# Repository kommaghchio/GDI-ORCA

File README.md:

A flight controller for a drone, with support for 2 servo motors, based on the Hack Club blueprint guide found here:
https://blueprint.hackclub.com/starter-projects/flightcontroller

I used KiCad, from which I used easyeda2kicad in order to get the footprints and schematic symbols, credited here:

https://github.com/uPesy/easyeda2kicad.py

It uses the STM32F722RET6 as the main brains.

Schematics:

PCB:

3D Board render:

BOM:
|Item                    |Qty|Supplier|Cost/item|Total Cost|link                                                                              |
|------------------------|---|--------|---------|----------|----------------------------------------------------------------------------------|
|USB-C 16 pin            |1  |LCSC    |$1.44    |$1.44     |https://www.lcsc.com/product-detail/C2765186.html?s_z=n_q_C2765186%2520USB-C      |
|C49441431 MicroSD       |1  |LCSC    |$0.44    |$0.44     |https://www.lcsc.com/product-detail/C49441431.html?s_z=n_q_C49441431%2520MicroSD  |
|C109322 TPS63070        |1  |LCSC    |$1.24    |$1.24     |https://www.lcsc.com/product-detail/C109322.html?s_z=n_q_C109322%2520TPS63070     |
|C5185863 LMR51430       |1  |LCSC    |$0.79    |$0.79     |https://www.lcsc.com/product-detail/C5185863.html?s_z=n_q_C5185863%2520LMR51430   |
|C544362 BQ25883         |1  |LCSC    |$4.26    |$4.26     |https://www.lcsc.com/product-detail/C544362.html?s_z=n_q_C544362%2520BQ25883      |
|C118207 STM32F722RET6   |1  |LCSC    |$11.29   |$11.29    |https://www.lcsc.com/product-detail/C118207.html?s_z=n_q_C118207%2520STM32F722RET6|
|C22459454 ICM-45686     |1  |LCSC    |$10.31   |$10.31    |https://www.lcsc.com/product-detail/C22459454.html?s_z=n_q_C22459454%2520ICM-45686|
|C22391138 BMP580        |1  |LCSC    |$1.21    |$1.21     |https://www.lcsc.com/product-detail/C22391138.html?s_z=n_q_C22391138%2520BMP580   |
|C2681587 5.8-ZSGT       |2  |LCSC    |$0.48    |$0.96     |https://www.lcsc.com/product-detail/C2681587.html?s_z=n_q_p_C2681587%25205.8-ZSGT |
|C7417180 1.5uH          |1  |LCSC    |$5.50    |$5.50     |https://www.lcsc.com/product-detail/C7417180.html?s_z=n_q_C7417180%25201.5uH      |
|C380178 5.6uH           |1  |LCSC    |$0.57    |$0.57     |https://www.lcsc.com/product-detail/C380178.html?s_z=n_q_C380178%25205.6uH        |
|C1857257 KC2520Z        |1  |LCSC    |$3.00    |$3.00     |https://www.lcsc.com/product-detail/C1857257.html?s_z=n_q_p_C1857257%2520KC2520Z  |
|PCB                     |1  |JLCPCB  |$9.20    |$9.20     |https://jlcpcb.com/                                                               |
|Estimated total shipping|1  |        |         |$9.45     |                                                                                  |

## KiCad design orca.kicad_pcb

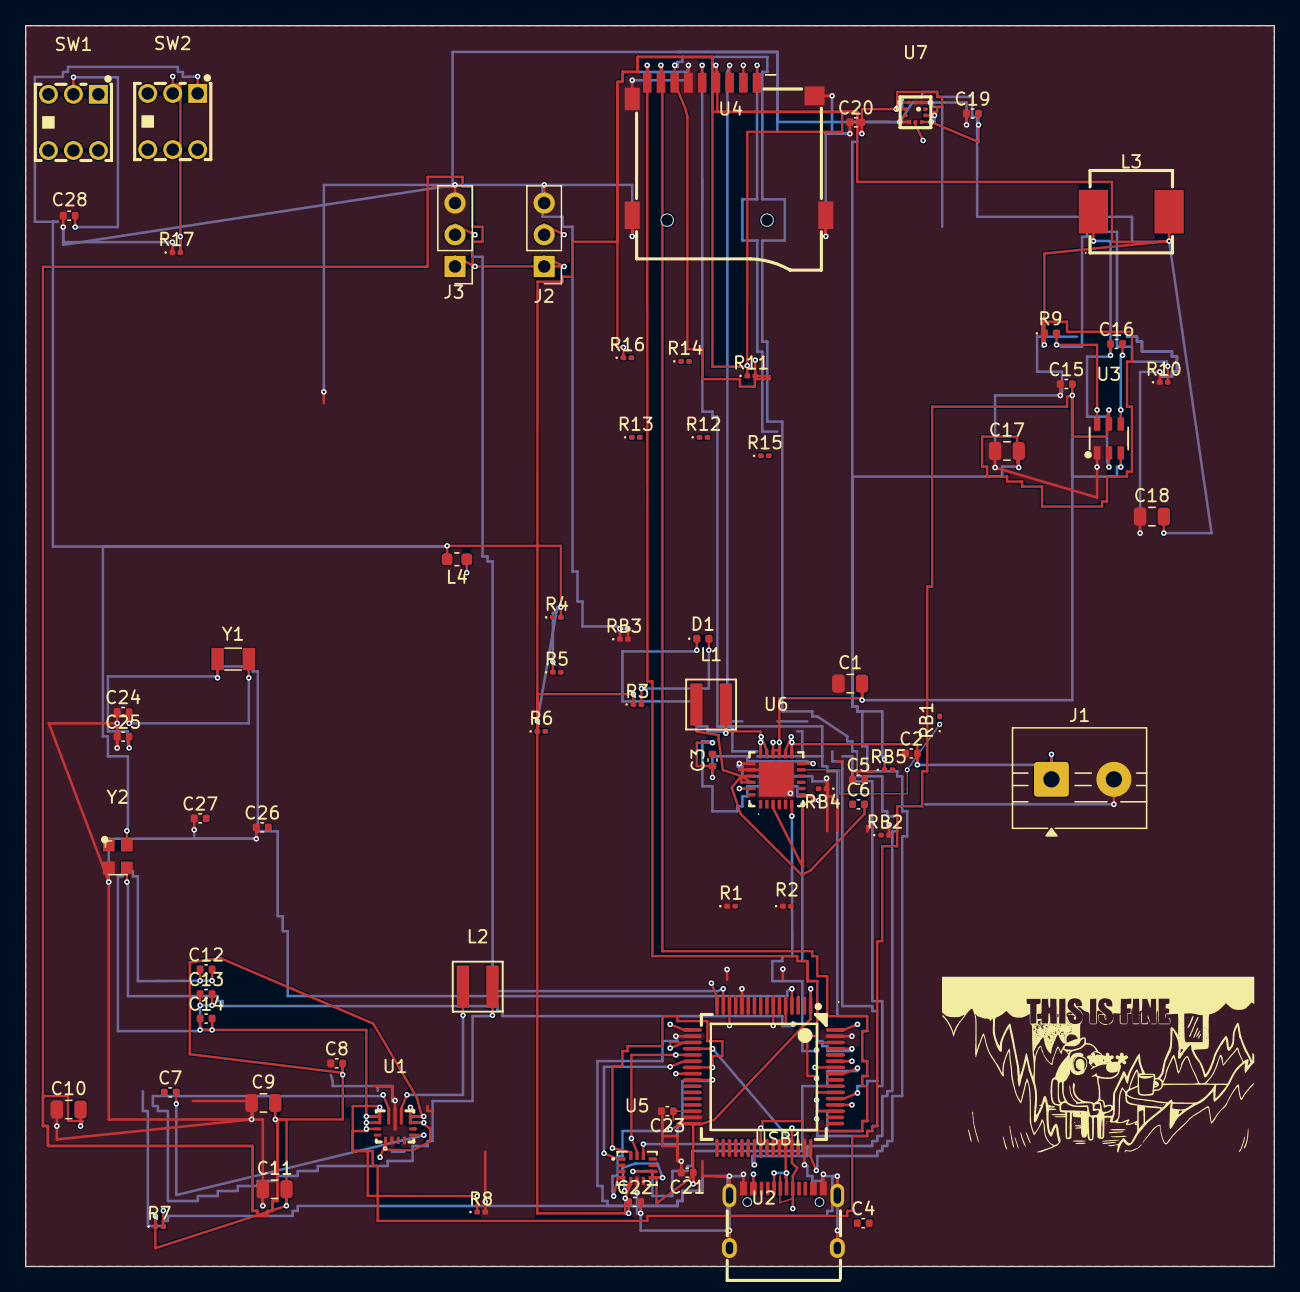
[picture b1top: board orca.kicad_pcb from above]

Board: 2 copper layers, 100.0 x 99.4 mm, 70 parts (0 on the bottom side), 51 nets.

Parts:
C1: 44uF; C_0805_2012Metric
C2, C6, C8, C12, C13, C14: 10uF; C_0402_1005Metric
C3: 47nF; C_0402_1005Metric
C4: 1nF; C_0402_1005Metric
C5: 10nF; C_0402_1005Metric
C7, C16, C19, C20, C21, C22, C28: 100nF; C_0402_1005Metric
C9, C10, C11, C17, C18: 22uF; C_0805_2012Metric
C15, C23: 2.2uF; C_0402_1005Metric
C24, C25: 6.8pF; C_0402_1005Metric
C26, C27: 20pF; C_0402_1005Metric
D1: LED; D_0402_1005Metric
J1: Screw_Terminal_01x02; TerminalBlock_MaiXu_MX126-5.0-02P_1x02_P5.00mm
J2, J3: Conn_01x03; PinHeader_1x03_P2.54mm_Vertical
L1, L2: 1.5 uH; 1.5uH
L3: 5.6uH
L4: FCM1608KF-601T03; L_0603_1608Metric
R1: 5.1K; D_0201_0603Metric
R2: 5.1k; D_0201_0603Metric
R3, R4, R5, R6, R7, R8, R11, R12, R13, R14, R15, R16, R17: 10K; D_0201_0603Metric
R9: 100K; D_0402_1005Metric
R10: 22.1K; D_0201_0603Metric
RB1: 5.23K; D_0201_0603Metric
RB2: 30.1K; D_0201_0603Metric
RB3, RB5: 10K; D_0201_0603Metric
RB4: 3B3; D_0201_0603Metric
SW1, SW2: SW_SPST; 5.8-ZSGT
U1: TPS63070RNMR; TPS63070
U2: STM32F722RET6
U3: LMR51430XDDCR; LMR51430
U4: JBL-102010052; MicroSD
U5: ICM-45686
U6: BQ25883RGER; BQ25883
U7: BMP580
USB1: TYPE-C 16PIN 2MD; USB-C
Y1: Q13FC1350000400; Crystal_SMD_3215-2Pin_3.2x1.5mm
Y2: KC2520Z

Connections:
+3.3V: C17.2, C18.2, C19.2, C20.2, C21.1, C22.1, L3.2, L4.2, R3.1, R4.2, R5.1, R6.1, R9.1, R11.1, R16.1, RB5.1, SW2.1 (A), U2.1 (VBAT), U2.19 (VDD), U2.32 (VDD), U2.48 (VDD), U2.64 (VDD), U4.4 (VDD), U5.5 (VDDIO), U5.8 (VDD), U7.1 (VDDIO), U7.5 (SDO), U7.6 (CSB), U7.10 (VDD), Y2.4 (VCC)
+5V: C8.2, C9.2, C10.2, C11.2, J2.1, J3.1, R7.1, U1.1 (PS/SYNC), U1.7 (Vout)
+BATT: C2.2, J1.1, U6.13 (BAT), U6.14 (BAT)
/BMP_INT: U2.24 (PC4), U7.7 (INT)
/BOOT: R17.2, SW2.2 (B), U2.60 (BOOT0)
/BQ_CE: U2.61 (PB8), U6.3 (~CE)
/BQ_INT: U2.62 (PB9), U6.6 (~INT)
/BTST: C3.2, U6.12 (BTST)
/HSE_IN: U2.5 (PH0-OSC_IN), Y2.3 (CLK)
/I2C_SCL: U2.58 (PB6), U6.5 (SCL), U7.2 (SCK)
/I2C_SDA: U2.59 (PB7), U6.4 (SDA), U7.4 (SDI)
/ICM_CS: U2.20 (PA4), U5.12 (AP_CS)
/ICM_INT1: U2.25 (PB0), U5.4 (INT1/INT)
/ICM_INT2: U2.57 (PB5), U5.9 (INT2/FSYNC/CLKIN)
/ICM_SCK: U2.21 (PA5), U5.13 (AP_SCL/AP_SCLK)
/ICM_SDI: U2.23 (PA7), U5.14 (AP_SDA/AP_SDIO/AP_SDI)
/ICM_SDO: U2.22 (PA6), U5.1 (AP_SDO/AP_AD0)
/LSE_IN: C24.2, U2.3 (PC14-OSC32_IN), Y1.1
/LSE_OUT: C25.2, U2.4 (PC15-OSC32_OUT), Y1.2
/RESET: C28.2, SW1.2 (B), U2.7 (NRST)
/SD_CD: U2.55 (PB3), U4.CD
/SD_CLK: U2.53 (PC12), U4.5 (CLK)
/SD_CMD: U2.54 (PD2), U4.3 (CMD)
/SD_DAT0: R11.2, U2.39 (PC8), U4.7 (DAT0)
/SD_DAT1: U2.40 (PC9), U4.8 (DAT1)
/SD_DAT2: U2.51 (PC10), U4.1 (DAT2)
/SD_DAT3: U2.52 (PC11), U4.2 (CD/DAT3)
/SERVO1: J2.2, U2.14 (PA0-WKUP)
/SERVO2: J3.2, U2.15 (PA1)
/USB_DN: U2.44 (PA11), USB1.A7 (Dn1), USB1.B7 (Dn2)
/USB_DP: U2.45 (PA12), USB1.A6 (Dp1), USB1.B6 (Dp2)
/VBUS: U6.23 (VBUS), USB1.A4B9 (VBUS), USB1.B4A9 (VBUS)
/VDDA: L4.1, U2.13 (VDDA)
/VREGN: RB1.1, U6.11 (REGN)
/VSYS: C1.2, C12.1, C12.2, C13.1, C13.2, C14.1, C14.2, C15.2, R8.1, U1.12 (Vin), U1.14 (EN), U3.3 (VIN), U3.5 (EN), U6.15 (SYS), U6.16 (SYS)
GND: C1.1, C2.1, C5.1, C8.1, C9.1, C10.1, C11.1, C15.1, C17.1, C18.1, C19.1, C20.1, C21.2, C22.2, C23.2, C24.1, C25.1, C26.1, C27.1, C28.1, J1.2, J2.3, J3.3, R1.1, R2.1, R8.2, R10.1, R17.1, RB2.2, RB3.1, RB3.2, RB4.1, U1.2 (PG), U1.4 (GND), U1.10 (PGND), U2.12 (VSSA), U2.18 (VSS), U2.31 (VSS), U2.47 (VSS), U2.63 (VSS), U3.1 (GND), U4.6 (VSS), U4.9 (GND), U4.10 (GND), U4.11 (GND), U4.12 (GND), U5.6 (GND), U6.19 (GND), U6.20 (GND), U6.25 (EP), U7.3 (VSS), U7.8 (VSS), U7.9 (VSS), USB1.13 (EH), USB1.14 (EH), USB1.A1B12 (GND), USB1.B1A12 (GND), Y2.2 (GND)
unnamed: C3.1, U6.7 (TS)
unnamed: C6.2, L1.1, U6.21 (PMID), U6.22 (PMID)
unnamed: C7.2, U1.5 (FB)
unnamed: C16.1, L3.1, U3.2 (SW)
unnamed: C16.2, U3.4 (FB)
unnamed: C23.1, U2.30 (VCAP_1)
unnamed: D1.1 (K), L1.2, U6.17 (SW), U6.18 (SW)
unnamed: D1.2 (A), R3.2
unnamed: L2.1, U1.9 (L2)
unnamed: L2.2, U1.11 (L1)
unnamed: R1.2, USB1.A5 (CC1)
unnamed: R2.2, USB1.B5 (CC2)
unnamed: R7.2, U1.6 (FB2)
unnamed: R9.2, R10.2, U3.6 (CB)
unnamed: U2.16 (PA2), U2.17 (PA3)

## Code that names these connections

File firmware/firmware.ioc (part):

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Mcu.Name=STM32F722R(C-E)Tx
Mcu.Package=LQFP64
Mcu.UserName=STM32F722RETx
PA0-WKUP.Signal=S_TIM2_CH1_ETR
PA1.Signal=S_TIM2_CH2
PA11.Mode=Host_Only
PA11.Signal=USB_OTG_FS_DM
PA12.Mode=Host_Only
PA12.Signal=USB_OTG_FS_DP
PA4.Mode=NSS_Signal_Hard_Input
PA4.Signal=SPI1_NSS
PA5.Mode=Full_Duplex_Master
PA5.Signal=SPI1_SCK
PA6.Mode=Full_Duplex_Master
PA6.Signal=SPI1_MISO
PA7.Mode=Full_Duplex_Master
PA7.Signal=SPI1_MOSI
PB0.Signal=GPXTI0
PB3.Signal=GPIO_Input
PB5.Signal=GPXTI5
PB6.Mode=I2C
PB6.Signal=I2C1_SCL
PB7.Mode=I2C
PB7.Signal=I2C1_SDA
PB8.Signal=GPIO_Output
PB9.Signal=GPXTI9
PC10.Mode=SD_4_bits_Wide_bus
PC10.Signal=SDMMC1_D2
PC11.Mode=SD_4_bits_Wide_bus
PC11.Signal=SDMMC1_D3
PC12.Mode=SD_4_bits_Wide_bus
PC12.Signal=SDMMC1_CK
PC14-OSC32_IN.Mode=LSE-External-Oscillator
PC14-OSC32_IN.Signal=RCC_OSC32_IN
PC15-OSC32_OUT.Mode=LSE-External-Oscillator
PC15-OSC32_OUT.Signal=RCC_OSC32_OUT
PC4.Signal=GPXTI4
PC8.Mode=SD_4_bits_Wide_bus
PC8.Signal=SDMMC1_D0
PC9.Mode=SD_4_bits_Wide_bus
PC9.Signal=SDMMC1_D1
PD2.Mode=SD_4_bits_Wide_bus
PD2.Signal=SDMMC1_CMD
PH0-OSC_IN.Mode=HSE-External-Oscillator
PH0-OSC_IN.Signal=RCC_OSC_IN
PH1-OSC_OUT.Mode=HSE-External-Oscillator
PH1-OSC_OUT.Signal=RCC_OSC_OUT
RCC.HSE_VALUE=25000000
board=custom
